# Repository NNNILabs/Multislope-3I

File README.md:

# Multislope 3I 
## Introduction
This repository contains hardware and software files for the third multislope prototype board, designated 3I. This is the most complete and proper version of the PCB so far, including a proper 8-resistor network, an LM399/ADR1399 reference, composite integrator (with two SOIC-8 footprints), shielding on the integrator summing node and test points to easily probe crucial nodes. 
History and operation are documented extensively [here](https://hackaday.io/project/190528-multislope-adc).
## Project Motivation
The second prototype PCB was completed hastily with not much thought put into either layout or choice of parts, so a better-designed (and hopefully better-evaluated) board was in order. 
## Usage
The KiCAD project files can be used to generate gerber files, which can be used to manufacture the PCBs. The code is written in C/C++ in the VScode development environment. Detailed instructions on how to compile the software will be added later. A .uf2 file is present in the project outputs which can be uploaded directly to the Pi Pico. 
## List of Files
- Hardware: KiCAD PCB design files, BOM and schematic. 

- Software: C/C++ code, uf2 file for direct upload. 
- Resources: Infographics
## Application Examples
- The readings from the overall converter (PWM counts and residue) were noisy, and the raw readings from the MCP3202 residue ADC were noisy and contained unexplained banding. Linearity shows a parabolic curve, probably because of wrong constants or small mismatches in switch resistances. 
### Linearity

### MCP3202 Raw Data (Detail)

### Cause
- Reading noise was [determined](https://hackaday.io/project/190528-multislope-adc/log/218489-a-path-forward) to be caused by poor layout and decoupling around the MCP3202 residue ADC. 
- Linearity bell curve could be caused by input resistor's PCR.
## Notes
- An interactive Excel document is provided in the Resources folder, with a slider to vary the residue constant to visually determine the best constant to reconcile runup and residue readings. Update: Excel file broke somehow, but you can still see the effect of moving the slider in the video linked below, timestamp [10:15](https://youtu.be/aNtOfKR7sto?t=615).
- Another version of the converter is in development, with improvements to speed, resolution and noise. 
## Links
https://www.youtube.com/watch?v=aNtOfKR7sto

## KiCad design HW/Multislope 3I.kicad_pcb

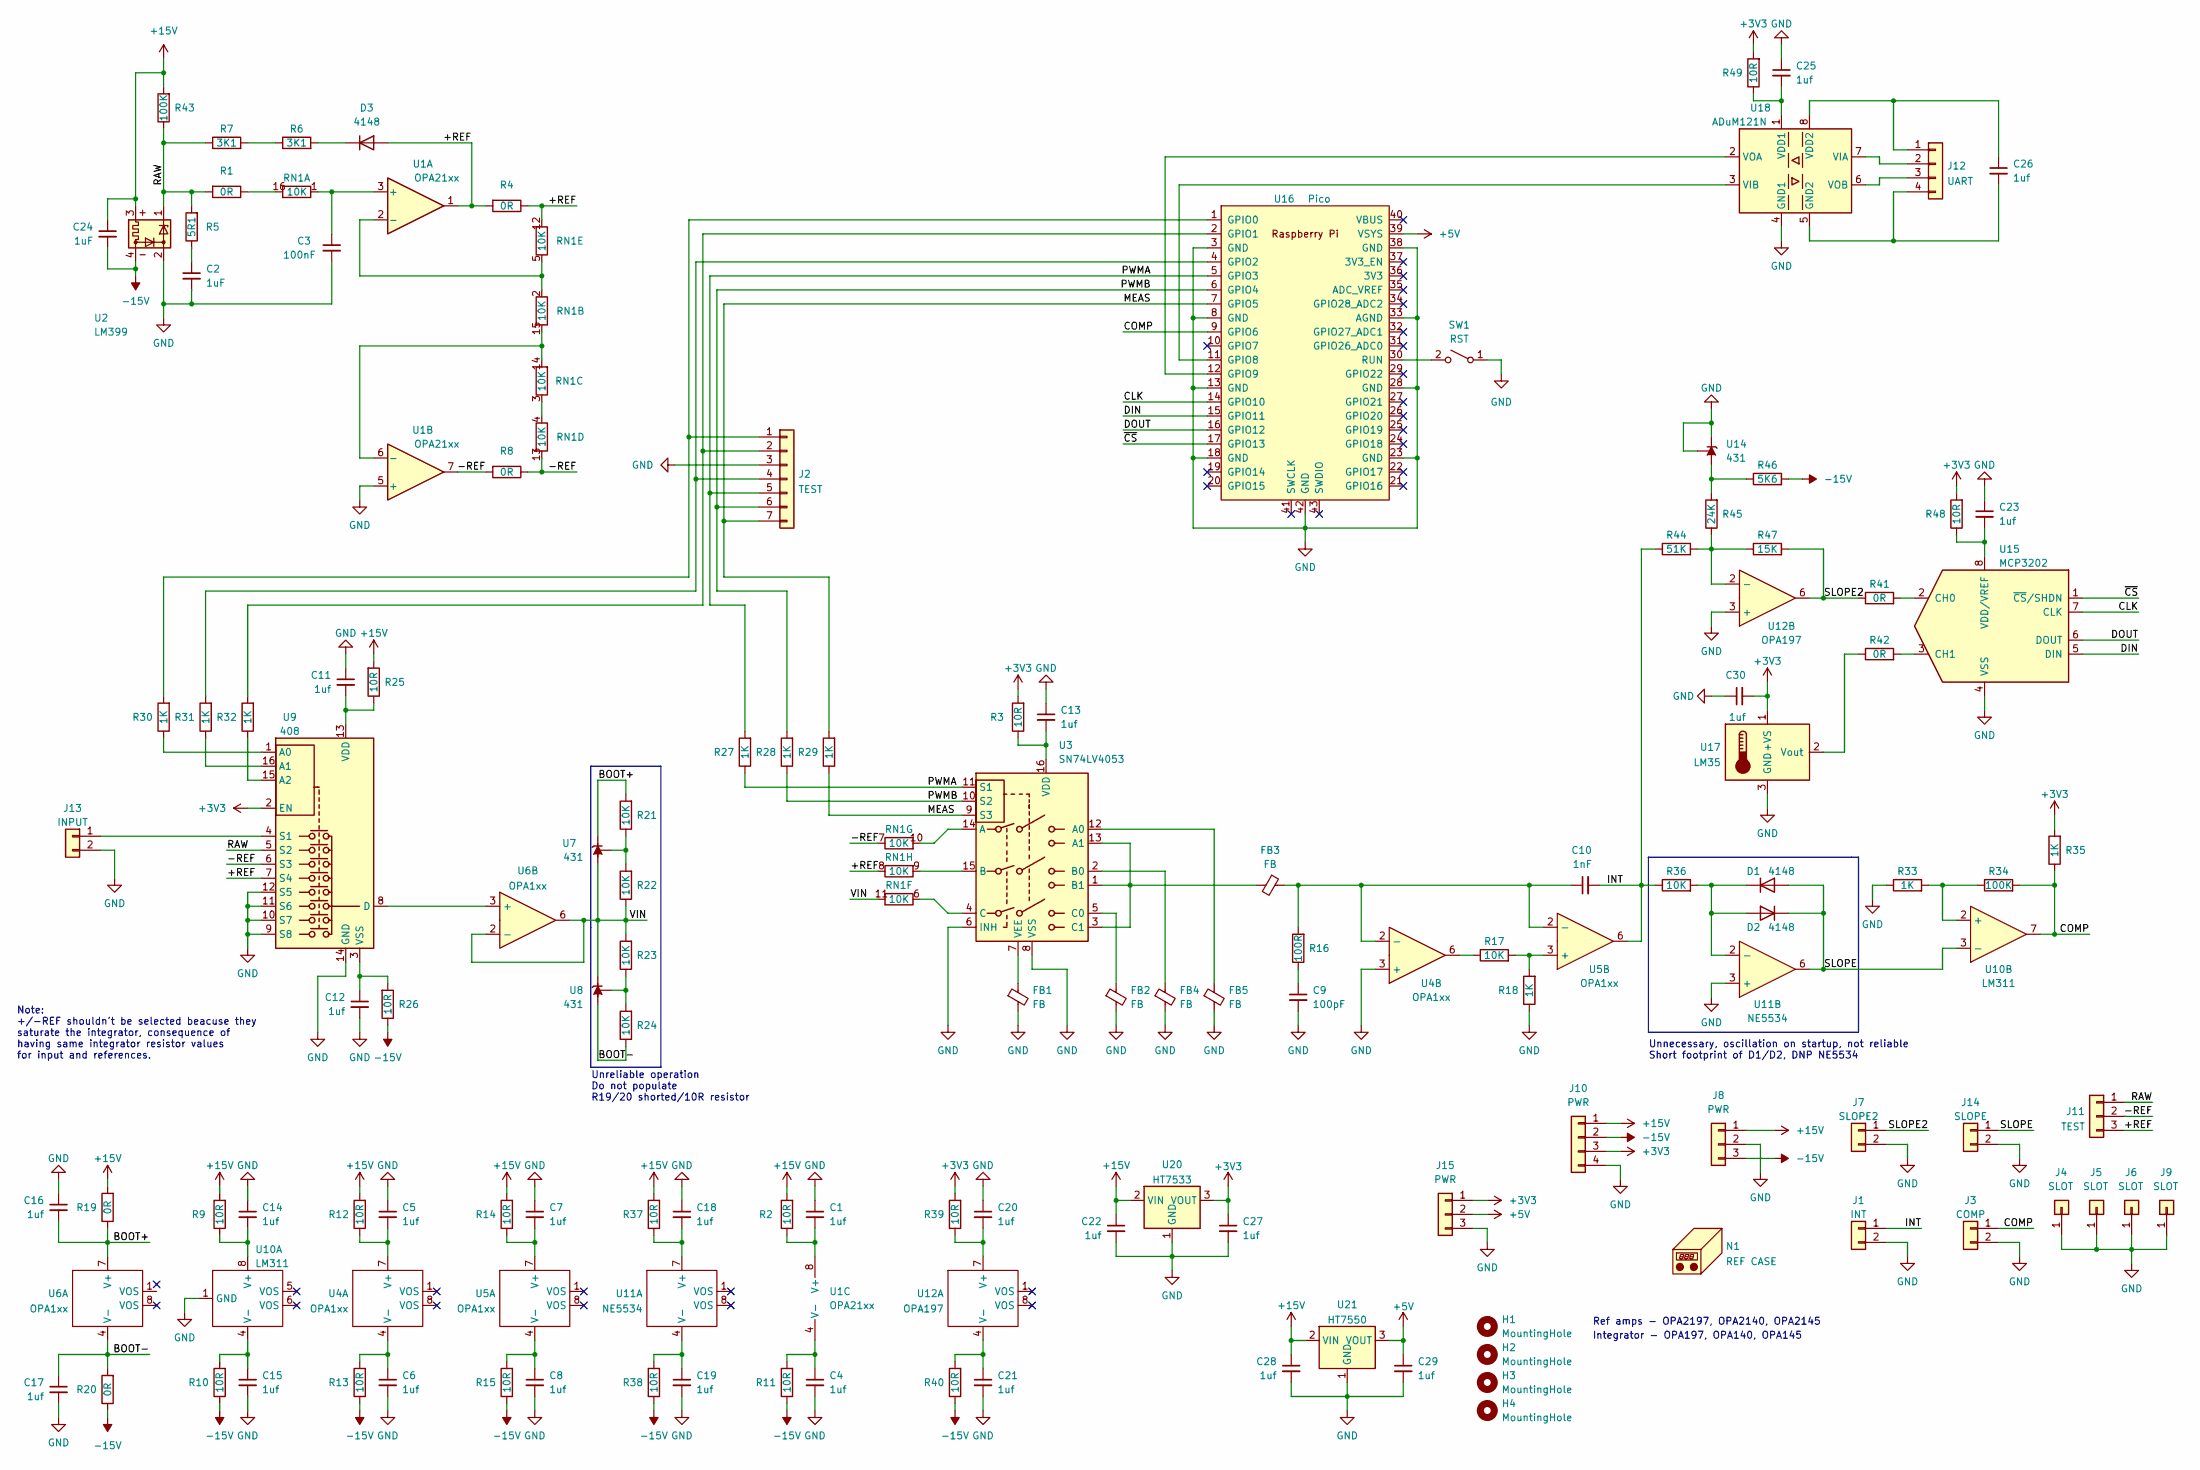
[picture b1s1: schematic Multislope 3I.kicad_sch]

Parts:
C1, C4, C5, C6, C7, C8, C11, C12, C13, C14, C15, C16, C17, C18, C19, C20, C21, C22, C23, C25, C26, C27, C28, C29, C30: 1uf; R_0603_1608Metric
C2: 1uF; R_0603_1608Metric
C3: 100nF; R_0603_1608Metric
C9: 100pF; R_0603_1608Metric
C10: 1nF; R_0603_1608Metric
C24: 1uF; C_0805_2012Metric
D1, D2, D3: 4148; D_SOD-323
FB1, FB2, FB3, FB4, FB5: FB; R_0603_1608Metric
H1, H2, H3, H4: MountingHole; MountingHole_3.2mm_M3_Pad_Via
J1: INT; PinHeader_1x02_P2.54mm_Vertical
J2: TEST; PinHeader_1x07_P2.54mm_Vertical
J3: COMP; PinHeader_1x02_P2.54mm_Vertical
J4, J5, J6, J9: SLOT; PinHeader_1x01_P2.54mm_Vertical
J7: SLOPE2; PinHeader_1x02_P2.54mm_Vertical
J8, J15: PWR; PinHeader_1x03_P2.54mm_Vertical
J10: PWR; PinHeader_1x04_P2.54mm_Vertical
J11: TEST; PinHeader_1x03_P2.54mm_Vertical
J12: UART; PinHeader_1x04_P2.54mm_Vertical
J13: INPUT; PinHeader_1x02_P2.54mm_Vertical
J14: SLOPE; PinHeader_1x02_P2.54mm_Vertical
N1: REF CASE; Ref Case
R1, R4, R8: 0R; R_0603_1608Metric
R2, R3, R9, R10, R11, R12, R13, R14, R15, R25, R26, R37, R38, R39, R40, R48, R49: 10R; R_0603_1608Metric
R5: 5R1; R_0603_1608Metric
R6, R7: 3K1; 0603 Jumper
R16: 100R; R_0603_1608Metric
R17, R21, R22, R23, R24, R36: 10K; R_0603_1608Metric
R18, R27, R28, R29, R30, R31, R32, R33, R35: 1K; R_0603_1608Metric
R19, R20, R41, R42: 0R; 0603 Jumper
R34, R43: 100K; R_0603_1608Metric
R44: 51K; R_0603_1608Metric
R45: 24K; R_0603_1608Metric
R46: 5K6; R_0603_1608Metric
R47: 15K; R_0603_1608Metric
RN1: 10K; SOIC-16_3.9x9.9mm_P1.27mm
SW1: RST; SW_Push_1P1T_NO_CK_KMR2
U1: OPA21xx; SOIC-8_3.9x4.9mm_P1.27mm
U2: LM399; Analog_TO-46-4_ThermalShield
U3: SN74LV4053; SOIC-16_3.9x9.9mm_P1.27mm
U4, U5, U6: OPA1xx; SOIC-8_3.9x4.9mm_P1.27mm
U7, U8, U14: 431; SOT-23
U9: 408; SOIC-16_3.9x9.9mm_P1.27mm
U10: LM311; SOIC-8_3.9x4.9mm_P1.27mm
U11: NE5534; SOIC-8_3.9x4.9mm_P1.27mm
U12: OPA197; SOIC-8_3.9x4.9mm_P1.27mm
U15: MCP3202; SOIC-8_3.9x4.9mm_P1.27mm
U16: Pico; RPi_Pico_SMD_TH
U17: LM35; TO-92
U18: ADuM121N; SOIC-8_3.9x4.9mm_P1.27mm
U20: HT7533; SOT-89-3
U21: HT7550; SOT-89-3

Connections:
+3V3: C27.1, C30.2, J10.3, J15.1, R3.2, R35.2, R39.2, R48.2, R49.2, U9.2 (EN), U17.1 (+VS), U20.3 (VOUT)
+5V: C29.1, J15.2, U16.39 (VSYS), U21.3 (VOUT)
+15V: C22.1, C24.1, C28.1, J8.1, J10.1, R2.2, R9.2, R12.2, R14.2, R19.2, R25.2, R37.2, R43.2, U2.3, U20.2 (VIN), U21.2 (VIN)
-15V: C24.2, J8.3, J10.2, R10.1, R11.1, R13.1, R15.1, R20.1, R26.1, R38.1, R40.1, R46.2, U2.4
/+REF: D3.2 (A), J11.3, R4.1, R4.2, RN1.8 (R8.1), RN1.12 (R5.2), U1.1, U9.7 (S4)
/-REF: J11.2, R8.1, R8.2, RN1.7 (R7.1), RN1.13 (R4.2), U1.7, U9.6 (S3)
/BOOT+: C16.2, R19.1, R21.2, U6.7 (V+), U7.2 (K)
/BOOT-: C17.1, R20.2, R24.1, U6.4 (V-), U8.3 (A)
/COMP: J3.1, R34.2, R35.1, U10.7, U16.9 (GPIO6)
/INT: C10.2, J1.1, R36.1, R44.1, U5.6
/MEAS: J2.7, R29.1, R29.2, U3.9 (S3), U16.7 (GPIO5)
/PWMA: J2.5, R27.1, R27.2, U3.11 (S1), U16.5 (GPIO3)
/PWMB: J2.6, R28.1, R28.2, U3.10 (S2), U16.6 (GPIO4)
/RAW: J11.1, R1.2, R5.2, R7.1, R43.1, U2.1, U9.5 (S2)
/SLOPE: D1.2 (A), D2.1 (K), J14.1, U10.3 (-), U11.6
/SLOPE2: J7.1, R41.1, R47.2, U12.6
/VIN: R22.1, R23.2, RN1.11 (R6.2), U6.2 (-), U6.6, U7.3 (A), U8.2 (K)
GND: C1.1, C2.2, C3.2, C4.2, C5.1, C6.2, C7.1, C8.2, C9.2, C11.1, C12.2, C13.1, C14.1, C15.2, C16.1, C17.2, C18.1, C19.2, C20.1, C21.2, C22.2, C23.1, C25.1, C27.2, C28.2, C29.2, C30.1, FB1.2, FB2.2, FB4.2, FB5.2, J1.2, J2.3, J3.2, J4.1, J5.1, J6.1, J7.2, J8.2, J9.1, J10.4, J13.2, J14.2, J15.3, R18.1, R33.1, SW1.1 (A), U1.5 (+), U2.2, U3.6 (INH), U3.8 (VSS), U4.3 (+), U9.9 (S8), U9.10 (S7), U9.11 (S6), U9.12 (S5), U9.14 (GND), U10.1 (GND), U11.3 (+), U12.3 (+), U14.1 (REF), U14.2 (K), U15.4 (VSS), U16.3 (GND), U16.8 (GND), U16.13 (GND), U16.18 (GND), U16.23 (GND), U16.28 (GND), U16.33 (AGND), U16.38 (GND), U16.42 (GND), U17.3 (GND), U18.4 (GND1), U20.1 (GND), U21.1 (GND)
unnamed: C2.1, R5.1
unnamed: C9.1, R16.1
unnamed: D1.1 (K), D2.2 (A), R36.2, U11.2 (-)
unnamed: D3.1 (K), R6.2
unnamed: J2.1, R30.2, U16.1 (GPIO0)
unnamed: J2.2, R32.2, U16.2 (GPIO1)
unnamed: J2.4, R31.2, U16.4 (GPIO2)
unnamed: C26.1, J12.1, U18.8 (VDD2)
unnamed: J12.2, U18.7 (VIA)
unnamed: J12.3, U18.6 (VOB)
unnamed: C26.2, J12.4, U18.5 (GND2)
unnamed: J13.1, U9.4 (S1)
unnamed: R6.1, R7.2
unnamed: R17.1, U4.6
unnamed: C3.1, RN1.1 (R1.1), U1.3 (+)
unnamed: R1.1, RN1.16 (R1.2)
unnamed: RN1.2 (R2.1), RN1.5 (R5.1), U1.2 (-)
unnamed: RN1.14 (R3.2), RN1.15 (R2.2), U1.6 (-)
unnamed: RN1.3 (R3.1), RN1.4 (R4.1)
unnamed: RN1.6 (R6.1), U3.4 (C)
unnamed: RN1.10 (R7.2), U3.14 (A)
unnamed: RN1.9 (R8.2), U3.15 (B)
unnamed: SW1.2 (B), U16.30 (RUN)
unnamed: C1.2, R2.1, U1.8 (V+)
unnamed: C4.1, R11.2, U1.4 (V-)
unnamed: FB5.1, U3.12 (A0)
unnamed: FB3.2, U3.1 (B1), U3.3 (C1), U3.13 (A1)
unnamed: FB4.1, U3.2 (B0)
unnamed: FB2.1, U3.5 (C0)
unnamed: C13.2, R3.1, U3.16 (VDD)
unnamed: FB1.1, U3.7 (VEE)
unnamed: C5.2, R12.1, U4.7 (V+)
unnamed: C6.1, R13.2, U4.4 (V-)
unnamed: C10.1, FB3.1, R16.2, U4.2 (-), U5.2 (-)
unnamed: C7.2, R14.1, U5.7 (V+)
unnamed: C8.1, R15.2, U5.4 (V-)
unnamed: R17.2, R18.2, U5.3 (+)
unnamed: U6.3 (+), U9.8 (D)
unnamed: R21.1, R22.2, U7.1 (REF)
unnamed: R23.1, R24.2, U8.1 (REF)
unnamed: R30.1, U9.1 (A0)
unnamed: R31.1, U9.16 (A1)
unnamed: R32.1, U9.15 (A2)
unnamed: C11.2, R25.1, U9.13 (VDD)
unnamed: C12.1, R26.2, U9.3 (VSS)
unnamed: C14.2, R9.1, U10.8 (V+)
unnamed: C15.1, R10.2, U10.4 (V-)
unnamed: R33.2, R34.1, U10.2 (+)
unnamed: C18.2, R37.1, U11.7 (V+)
unnamed: C19.1, R38.2, U11.4 (V-)
unnamed: C20.2, R39.1, U12.7 (V+)
unnamed: C21.1, R40.2, U12.4 (V-)
unnamed: R44.2, R45.1, R47.1, U12.2 (-)
unnamed: R45.2, R46.1, U14.3 (A)
unnamed: R41.2, U15.2 (CH0)
unnamed: R42.2, U15.3 (CH1)
unnamed: U15.7 (CLK), U16.14 (GPIO10)
unnamed: U15.5 (DIN), U16.15 (GPIO11)
unnamed: U15.6 (DOUT), U16.16 (GPIO12)
unnamed: C23.2, R48.1, U15.8 (VDD/VREF)
unnamed: U15.1 (~CS/SHDN), U16.17 (GPIO13)
unnamed: U16.11 (GPIO8), U18.3 (VIB)
unnamed: U16.12 (GPIO9), U18.2 (VOA)
unnamed: R42.1, U17.2 (Vout)
unnamed: C25.2, R49.1, U18.1 (VDD1)

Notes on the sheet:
Ref amps - OPA2197, OPA2140, OPA2145
Unreliable operation Do not populate R19/20 shorted/10R resistor
Integrator - OPA197, OPA140, OPA145
Unnecessary, oscillation on startup, not reliable Short footprint of D1/D2, DNP NE5534
Note: +/-REF shouldn't be selected beacuse they saturate the integrator, consequence of having same integrator resistor values for input and references.

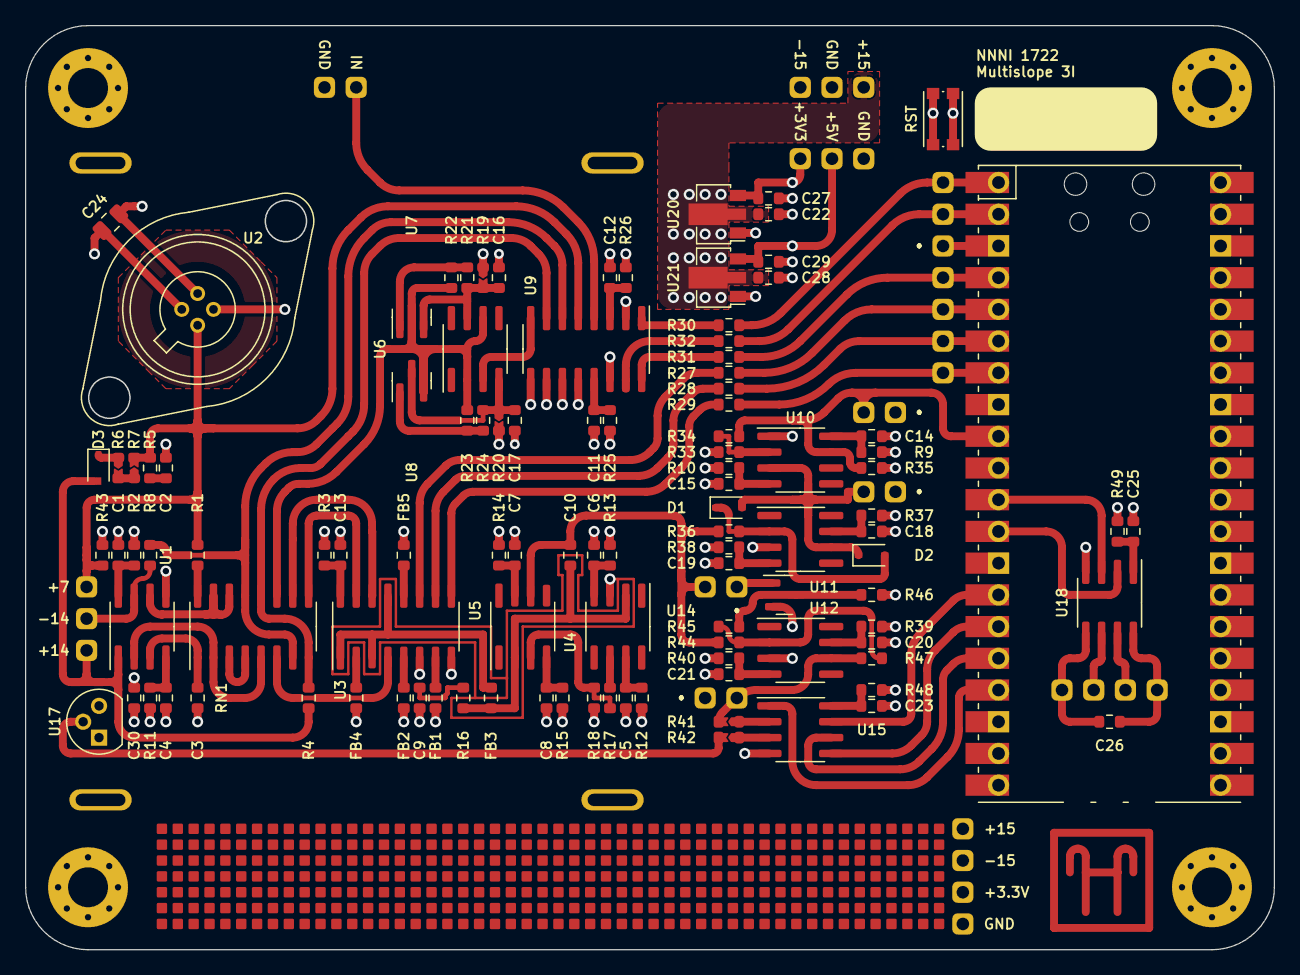
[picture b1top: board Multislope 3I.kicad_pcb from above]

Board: 4 copper layers, 100.0 x 74.0 mm, 128 parts (0 on the bottom side), 83 nets.

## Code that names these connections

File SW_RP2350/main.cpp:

#include <stdio.h>
#include "pico/stdlib.h"
#include "hardware/gpio.h"
#include "hardware/pio.h"
#include "hardware/irq.h"
#include "hardware/clocks.h"

#include "ms.pio.h"
#include "lib/i2c_slave.h"

const float div = 40;
uint32_t pwmCycles = 15000;

const uint8_t MUX_A0 = 0;
const uint8_t MUX_A1 = 2;
const uint8_t MUX_A2 = 1;

const uint8_t PWMA = 3;                // need to be next to each other
const uint8_t PWMB = 4;                // need to be next to each other
const uint8_t MEAS = 5;
const uint8_t COMP = 6;

// Pinout notes for TMT multislope
// TMUX1134:
// S1: RESET (somehow)
// S2: -VREF
// S3: +VREF
// S4: VIN

const double vrefAbs = 6.85793; // Measured using K2000

double voltage = 0.0;

PIO pio;

uint multislopeSM;
uint residueSM;
uint calibrationSM;
uint rundownSM;

int32_t counts = 0;
int32_t residueBefore = 0;
int32_t residueAfter = 0;
int32_t RUU = 1540;
int32_t RUD = 1540;
int32_t rundownUp = 0;
int32_t rundownDown = 0;

int32_t gndCounts = 0;
int32_t rawCounts = 0;
int32_t inCounts = 0;
int32_t previousGndCounts = 0;
int32_t finalGroundCounts = 0;

int32_t runup_pos = 0;
int32_t runup_neg = 0;
int32_t rundown_pos = 0;
int32_t rundown_neg = 0;
int32_t residue_before = 0;
int32_t residue_after = 0;

int32_t N1, N2, N3;

int32_t result = 0;

uint32_t newInput = 0;
char inputBuffer[32] = {0};

// MCP3202 ADC
#define CS   13
#define CLK  12
#define MOSI 11
#define MISO 10

#define LED  25

enum muxState
{
    MUX_IN, 
    MUX_RAW,
    MUX_GND,
    MUX_POSREF,  // Implement if input resistor is > 10kΩ
    MUX_NEGREF   // Same as above
};

void setMuxState(enum muxState inputState)
{
    switch(inputState)
    {
        case MUX_IN:
            gpio_put(MUX_A0, false);
            gpio_put(MUX_A1, false);
            gpio_put(MUX_A2, false);
            break;

        case MUX_RAW:
            gpio_put(MUX_A0, true);
            gpio_put(MUX_A1, false);
            gpio_put(MUX_A2, false);
            break;
        
        case MUX_GND:
            gpio_put(MUX_A0, false);
            gpio_put(MUX_A1, false);
            gpio_put(MUX_A2, true);
            break;
    }
}

void get_counts(uint32_t countNum)
{
    gpio_put(LED, true);

    pio_sm_clear_fifos(pio, multislopeSM);
    pio_sm_clear_fifos(pio, residueSM);

    pio_sm_put_blocking(pio, multislopeSM, countNum - 1);         // write number of PWM cycles to runup state machine

    residueBefore = pio_sm_get_blocking(pio, residueSM);          // read pre-runup integrator state

    counts = ~pio_sm_get_blocking(pio, multislopeSM);             // read runup counts
    rundownUp = ~pio_sm_get_blocking(pio, multislopeSM);          // read rundown up counts
    rundownDown = ~pio_sm_get_blocking(pio, multislopeSM);        // read rundown down counts

    residueAfter = pio_sm_get_blocking(pio, residueSM);           // read post-runup integrator state

    runup_pos = pwmCycles - counts;
    runup_neg = counts;

    rundown_neg = rundownUp - counts;
    rundown_pos = rundownDown - rundownUp;

    residue_before = residueBefore & 0xFFF;
    residue_after = residueAfter & 0xFFF;

    gpio_put(LED, false);
}

void get_cal()
{
    sleep_ms(100);

    gpio_put(LED, true);

    uint32_t countOne = 0;
    uint32_t countTwo = 0;
    uint32_t countThree = 0;
    uint32_t countFour = 0;

    pio_sm_put_blocking(pio, calibrationSM, 1);

    countOne = pio_sm_get_blocking(pio, residueSM);
    countTwo = pio_sm_get_blocking(pio, residueSM);
    countThree = pio_sm_get_blocking(pio, residueSM);

    pio_sm_clear_fifos(pio, calibrationSM);
    pio_sm_clear_fifos(pio, residueSM);

    uint32_t R1 = (countTwo - countOne);
    uint32_t R2 = (countTwo - countThree);

    RUU = R2; // * 1.0001; // R2;
    RUD = R1; // * 0.9999; // R1;

    gpio_put(LED, false);

}

void get_result()
{
    N1 = N2 = N3 = 0;

    // N1 = (runup_neg * (15*RUU + 1*RUD)) - (runup_pos * (1*RUU + 15*RUD)); // Complementary PWM runup
    N1 = (runup_neg * (14*RUU)) - (runup_pos * (14*RUD)); // Jaromir runup
    N2 = (rundown_neg * RUU) - (rundown_pos * RUD);
    N3 = residue_after - residue_before;

    result = N1 + N2 + N3;

}

int main() 
{
    set_sys_clock_khz(96000, true);
    stdio_init_all();

    i2c_init();

    gpio_init(LED);
    gpio_set_dir(LED, GPIO_OUT);

    gpio_init(MUX_A0);
    gpio_init(MUX_A1);
    gpio_init(MUX_A2);

    gpio_set_dir(MUX_A0, GPIO_OUT);
    gpio_set_dir(MUX_A1, GPIO_OUT);
    gpio_set_dir(MUX_A2, GPIO_OUT);
    
    sleep_us(10);

    gpio_init(13);
    gpio_set_dir(13, GPIO_OUT);
    gpio_put(13, false);

    pio = pio0;

    residueSM = 0; // pio_claim_unused_sm(pio, true);
    uint residueOffset = pio_add_program(pio, &residue_program);

    calibrationSM = 1; // pio_claim_unused_sm(pio, true);
    uint calibrationOffset = pio_add_program(pio, &calibration_program);

    residue_program_init(pio, residueSM, residueOffset, MISO, div);
    calibration_program_init(pio, calibrationSM, calibrationOffset, PWMA, COMP, div, MEAS);

    pio_sm_set_enabled(pio, calibrationSM, true);
    pio_sm_set_enabled(pio, residueSM, true);

    get_cal();

    sleep_ms(100);

    get_cal();

    // while(true)
    // {
    //     get_cal();
    //     sleep_ms(500);
    //     printf("%d, %d\n", RUU, RUD);
    // }

    pio_sm_set_enabled(pio, residueSM, false);
    pio_sm_set_enabled(pio, calibrationSM, false);

    pio_remove_program(pio, &calibration_program, calibrationOffset);
    pio_remove_program(pio, &residue_program, residueOffset);

    multislopeSM = pio_claim_unused_sm(pio, true);
    uint multislopeOffset = pio_add_program(pio, &ms_program);

    residueSM = pio_claim_unused_sm(pio, true);
    residueOffset = pio_add_program(pio, &residue_program);

    ms_program_init(pio, multislopeSM, multislopeOffset, PWMA, COMP, div, MEAS);
    residue_program_init(pio, residueSM, residueOffset, MISO, div);

    pio_sm_set_enabled(pio, multislopeSM, true);
    pio_sm_set_enabled(pio, residueSM, true);

    get_counts(50);

    sleep_ms(1000);

    setMuxState(MUX_GND);
    sleep_us(100);
    get_counts(pwmCycles);
    get_result();

    gndCounts = result;

    sleep_ms(100);

    setMuxState(MUX_RAW);
    sleep_us(100);
    get_counts(pwmCycles);
    get_result();

    rawCounts = result;

    sleep_ms(100);

    setMuxState(MUX_IN);

    while(true)
    {
        // newInput = scanf("%s", &inputBuffer, 31);         // Read input from serial port

        while(!regs.conversionStatus);

        // setMuxState(MUX_GND);

        // sleep_ms(1);
        // get_counts(pwmCycles);
        // get_result();

        // gndCounts = result;

        // setMuxState(MUX_IN);

        sleep_ms(1);
        get_counts(pwmCycles);
        get_result();

        inCounts = result;

        voltage = ((double)(inCounts - gndCounts)/(double)(rawCounts - gndCounts)) * vrefAbs;

        regs.output = voltage;
        sleep_ms(1);
        regs.conversionStatus = 0;

        // printf("%g\n", voltage);

        // printf("%d, %d, %d, %g\n", gndCounts, rawCounts, inCounts, voltage);

        // printf("%d, %d, %d\n", N1, N2, N3);

        // sleep_ms(500);

    }
    
    return 0;
}

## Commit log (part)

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2022-04-24 Added PCB files
2022-04-25 PCB compact-ified
2022-04-25 removed redundant files
2022-04-26 pcb completed
2022-04-26 'final' PCB
2022-04-26 minor mistakes fixed
2022-04-28 pcb final touches
2022-07-03 reoganized
2022-07-03 added basic pico program
2022-07-04 added MCP ACD code
2022-07-11 added PIO mulstislope code
2022-07-11 Schematic updated
2022-07-11 Reference startup circuit added
2022-07-11 fixed PIO stalling
2022-07-12 updated upload script
2022-07-18 Updated Schematic
2022-07-18 added code to print temperature
2022-07-18 added on command readout
2022-07-18 Updated test code
2022-07-19 added dithering
2022-07-19 Updated test software
2022-07-20 concept interrupt ADC code
2022-07-28 added experimental DMA ADC reading
2022-07-28 small PIO pin state fix
2022-08-02 fixed DMA not working after first cycle
2022-08-02 removed some redundant variables
2022-08-02 CS line now works
2022-08-02 removed degug messages
2022-08-02 updated cmake to include all libraries
2022-08-02 removed VScode specific settings
2022-08-02 did it propely this time
2022-08-03 gitignore fixes, added windows build script, fixed missing header reference
2022-08-03 Moved build script up one directory
2022-08-06 Updated Schematic PDF
2022-08-08 added RP2040 ADC output for testing
2022-08-10 updated math and debugging
2022-08-10 Software updated
2022-09-30 PCB Finalized
2023-01-06 updated files
2023-06-03 ms.pio
    - One small aesthetic change
    - Added MCP3202 SPI code with instructions, to do
2023-06-22 Optimized PIO Code 1
2023-10-13 updated file
2023-10-18 tried to do ADC SPI in PIO
2023-10-18 a few tweaks to the oversights in the PIO code
2024-07-01 Major code update 01.07.2024
    Restarted work on finishing this project after more than a year.
    Code was completely refactored. DMA/PIO interrupt was removed, and two state machines from the same PIO block were loaded with runup and (mock) residue code and sychronized using interrupt 0 (irq 0).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
2024-07-03 added files
2024-07-09 udpated files
2024-07-13 updated project log
2024-07-21 tried int rel without effect
2024-07-22 fixed residue ADC bug
    readings delayed by one cycle, fixed by clearing fifos before measurement
2024-07-24 on-board V calculation
2024-07-24 implemented internal calculation with gain and offset cal
2024-07-25 refactored code to fit with current SDK version
2024-07-25 restored project log
2024-07-26 fixed runup calculation issue
    Jaromir runup injects ±14 units worth of charge, not ±15
2024-08-13 Updated project.log with new theory about 100 NPLC INL error with Runup 2
2024-08-19 moved to pico vscode extension (slightly buggy)
2024-08-24 added RP2350 project
2024-08-28 updated project.log with TMT multislope noise results
2024-08-29 updated project.log with crystal and GPIO bug information
2024-09-20 12MHz crystal added, results noted
2024-10-03 test update
2024-10-11 updated project log, fixed RP2040 software
